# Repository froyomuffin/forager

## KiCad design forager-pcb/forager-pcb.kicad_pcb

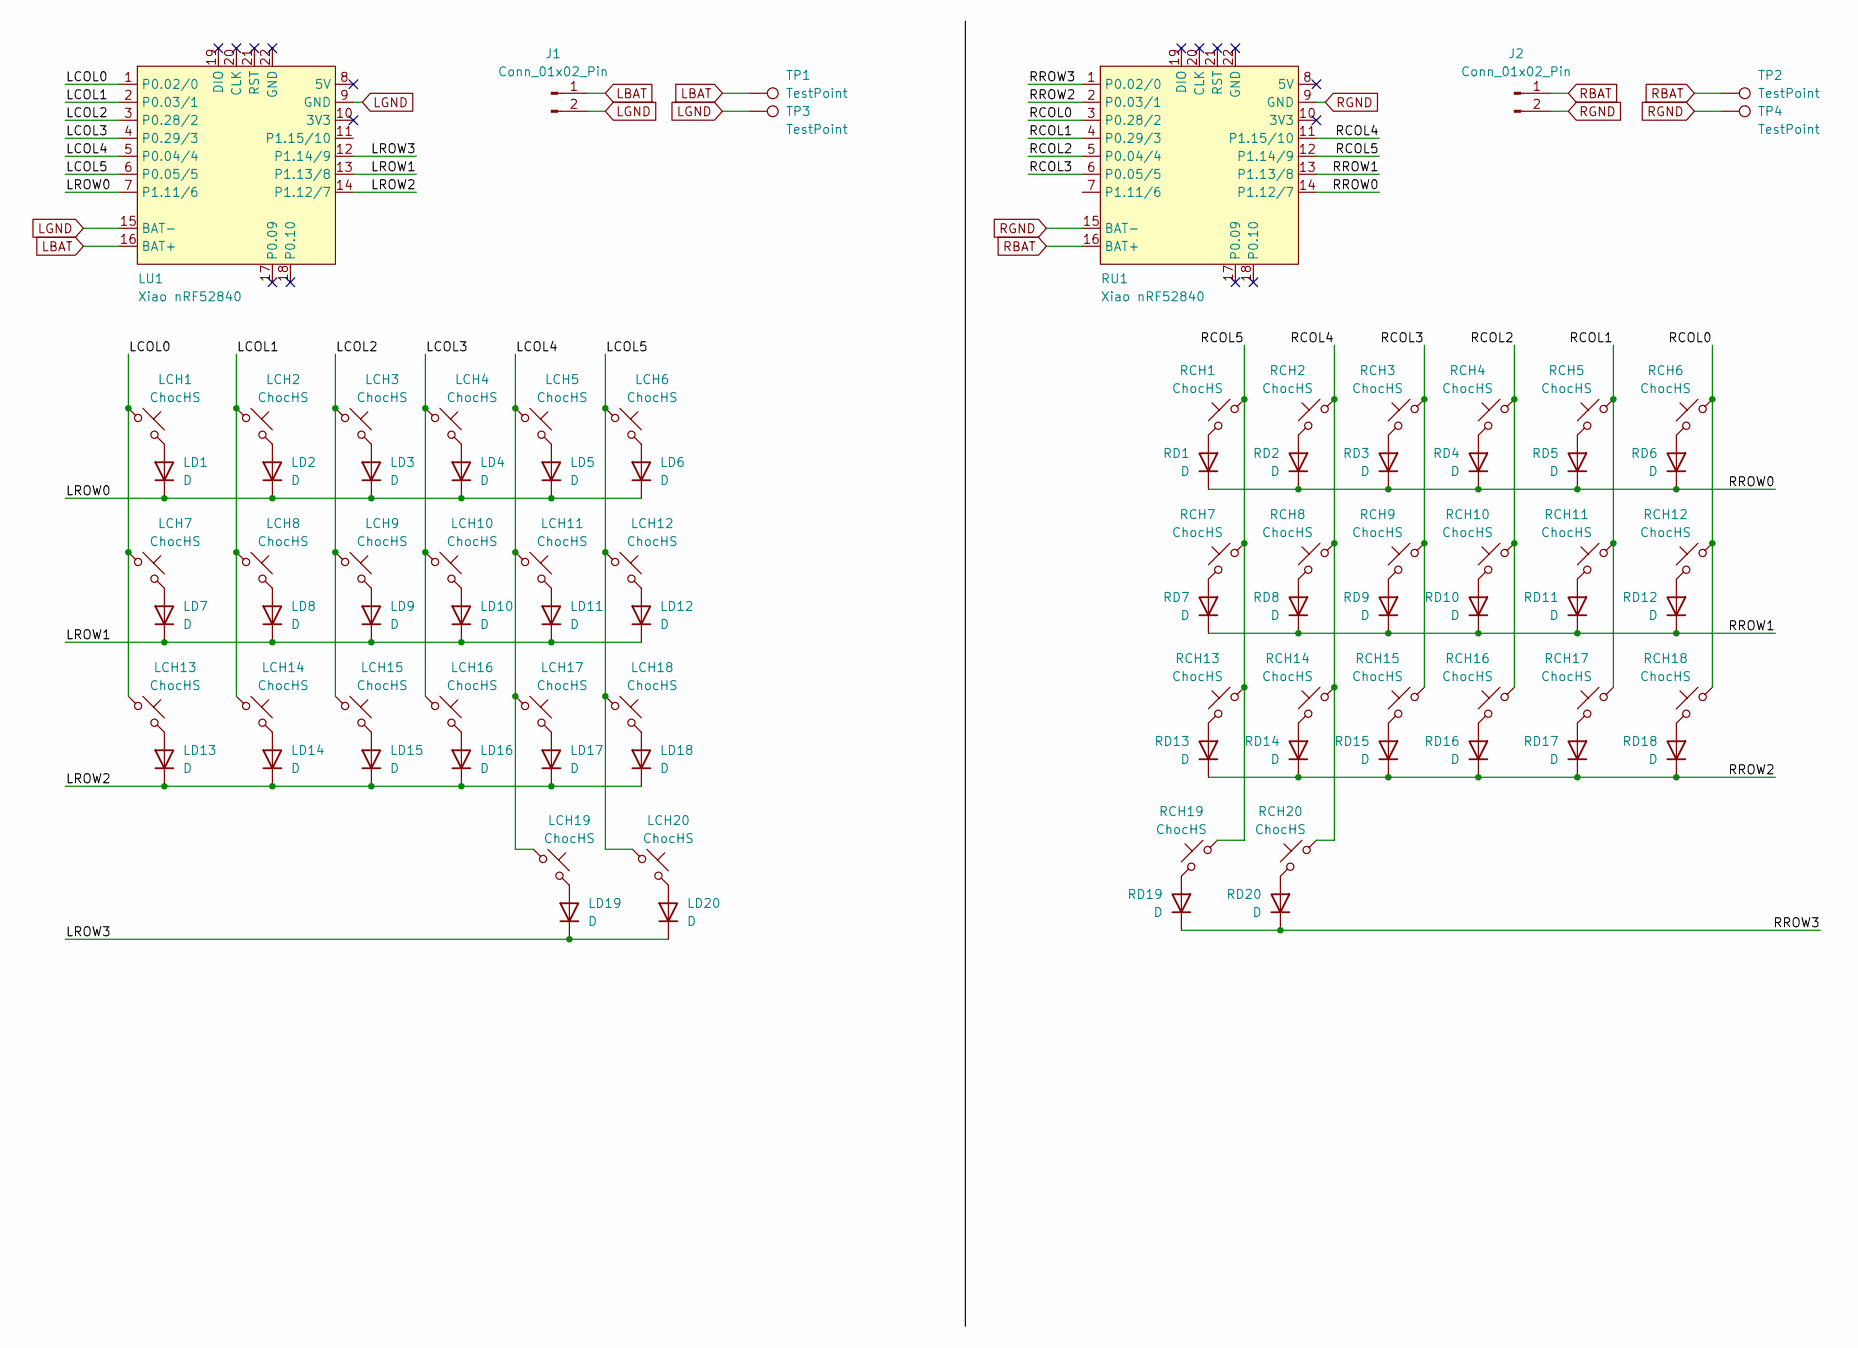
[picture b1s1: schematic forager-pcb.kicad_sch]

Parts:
J1, J2: Conn_01x02_Pin; JST_ACH_BM02B-ACHSS-GAN-ETF_1x02-1MP_P1.20mm_Vertical
LCH1, LCH2, LCH3, LCH4, LCH5, LCH6, LCH7, LCH8, LCH9, LCH10, LCH11, LCH12, LCH13, LCH14, LCH15, LCH16, LCH17, LCH18, LCH19, LCH20: ChocHS; Choc_v2_PG1353_socket
LD1, LD2, LD3, LD4, LD5, LD6, LD7, LD8, LD9, LD10, LD11, LD12, LD13, LD14, LD15, LD16, LD17, LD18, LD19, LD20: D; D_SOD-123
LU1: Xiao nRF52840; xiao-ble-smd-cutout
RCH1, RCH2, RCH3, RCH4, RCH5, RCH6, RCH7, RCH8, RCH9, RCH10, RCH11, RCH12, RCH13, RCH14, RCH15, RCH16, RCH17, RCH18, RCH19, RCH20: ChocHS; Choc_v2_PG1353_socket
RD1, RD2, RD3, RD4, RD5, RD6, RD7, RD8, RD9, RD10, RD11, RD12, RD13, RD14, RD15, RD16, RD17, RD18, RD19, RD20: D; D_SOD-123
RU1: Xiao nRF52840; xiao-ble-smd-cutout
TP1, TP2, TP3, TP4: TestPoint; TestPoint_Pad_D2.0mm

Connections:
/LCOL0: LCH1.1, LCH7.1, LCH13.1, LU1.1 (P0.02/0)
/LCOL1: LCH2.1, LCH8.1, LCH14.1, LU1.2 (P0.03/1)
/LCOL2: LCH3.1, LCH9.1, LCH15.1, LU1.3 (P0.28/2)
/LCOL3: LCH4.1, LCH10.1, LCH16.1, LU1.4 (P0.29/3)
/LCOL4: LCH5.1, LCH11.1, LCH17.1, LCH19.1, LU1.5 (P0.04/4)
/LCOL5: LCH6.1, LCH12.1, LCH18.1, LCH20.1, LU1.6 (P0.05/5)
/LROW0: LD1.1 (K), LD2.1 (K), LD3.1 (K), LD4.1 (K), LD5.1 (K), LD6.1 (K), LU1.7 (P1.11/6)
/LROW1: LD7.1 (K), LD8.1 (K), LD9.1 (K), LD10.1 (K), LD11.1 (K), LD12.1 (K), LU1.13 (P1.13/8)
/LROW2: LD13.1 (K), LD14.1 (K), LD15.1 (K), LD16.1 (K), LD17.1 (K), LD18.1 (K), LU1.14 (P1.12/7)
/LROW3: LD19.1 (K), LD20.1 (K), LU1.12 (P1.14/9)
/RCOL0: RCH6.1, RCH12.1, RCH18.1, RU1.3 (P0.28/2)
/RCOL1: RCH5.1, RCH11.1, RCH17.1, RU1.4 (P0.29/3)
/RCOL2: RCH4.1, RCH10.1, RCH16.1, RU1.5 (P0.04/4)
/RCOL3: RCH3.1, RCH9.1, RCH15.1, RU1.6 (P0.05/5)
/RCOL4: RCH2.1, RCH8.1, RCH14.1, RCH20.1, RU1.11 (P1.15/10)
/RCOL5: RCH1.1, RCH7.1, RCH13.1, RCH19.1, RU1.12 (P1.14/9)
/RROW0: RD1.1 (K), RD2.1 (K), RD3.1 (K), RD4.1 (K), RD5.1 (K), RD6.1 (K), RU1.14 (P1.12/7)
/RROW1: RD7.1 (K), RD8.1 (K), RD9.1 (K), RD10.1 (K), RD11.1 (K), RD12.1 (K), RU1.13 (P1.13/8)
/RROW2: RD13.1 (K), RD14.1 (K), RD15.1 (K), RD16.1 (K), RD17.1 (K), RD18.1 (K), RU1.2 (P0.03/1)
/RROW3: RD19.1 (K), RD20.1 (K), RU1.1 (P0.02/0)
LBAT: J1.1, LU1.16 (BAT+), TP1.1
LGND: J1.2, LU1.9 (GND), LU1.15 (BAT-), TP3.1
unnamed: LCH1.2, LD1.2 (A)
unnamed: LCH2.2, LD2.2 (A)
unnamed: LCH3.2, LD3.2 (A)
unnamed: LCH4.2, LD4.2 (A)
unnamed: LCH5.2, LD5.2 (A)
unnamed: LCH6.2, LD6.2 (A)
unnamed: LCH7.2, LD7.2 (A)
unnamed: LCH8.2, LD8.2 (A)
unnamed: LCH9.2, LD9.2 (A)
unnamed: LCH10.2, LD10.2 (A)
unnamed: LCH11.2, LD11.2 (A)
unnamed: LCH12.2, LD12.2 (A)
unnamed: LCH13.2, LD13.2 (A)
unnamed: LCH14.2, LD14.2 (A)
unnamed: LCH15.2, LD15.2 (A)
unnamed: LCH16.2, LD16.2 (A)
unnamed: LCH17.2, LD17.2 (A)
unnamed: LCH18.2, LD18.2 (A)
unnamed: LCH19.2, LD19.2 (A)
unnamed: LCH20.2, LD20.2 (A)
unnamed: RCH1.2, RD1.2 (A)
unnamed: RCH2.2, RD2.2 (A)
unnamed: RCH3.2, RD3.2 (A)
unnamed: RCH4.2, RD4.2 (A)
unnamed: RCH5.2, RD5.2 (A)
unnamed: RCH6.2, RD6.2 (A)
unnamed: RCH7.2, RD7.2 (A)
unnamed: RCH8.2, RD8.2 (A)
unnamed: RCH9.2, RD9.2 (A)
unnamed: RCH10.2, RD10.2 (A)
unnamed: RCH11.2, RD11.2 (A)
unnamed: RCH12.2, RD12.2 (A)
unnamed: RCH13.2, RD13.2 (A)
unnamed: RCH14.2, RD14.2 (A)
unnamed: RCH15.2, RD15.2 (A)
unnamed: RCH16.2, RD16.2 (A)
unnamed: RCH17.2, RD17.2 (A)
unnamed: RCH18.2, RD18.2 (A)
unnamed: RCH19.2, RD19.2 (A)
unnamed: RCH20.2, RD20.2 (A)
RBAT: J2.1, RU1.16 (BAT+), TP2.1
RGND: J2.2, RU1.9 (GND), RU1.15 (BAT-), TP4.1

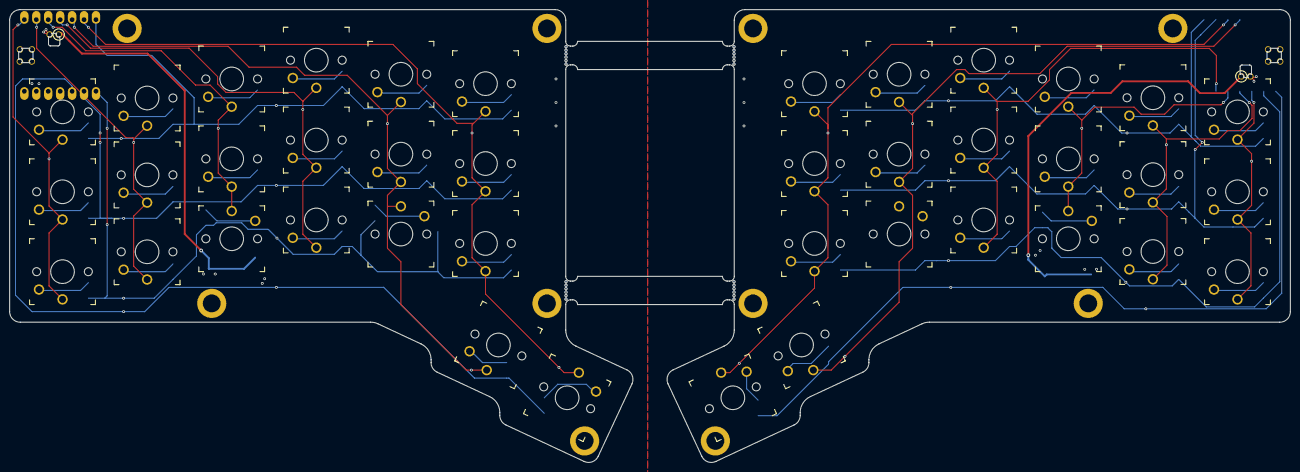
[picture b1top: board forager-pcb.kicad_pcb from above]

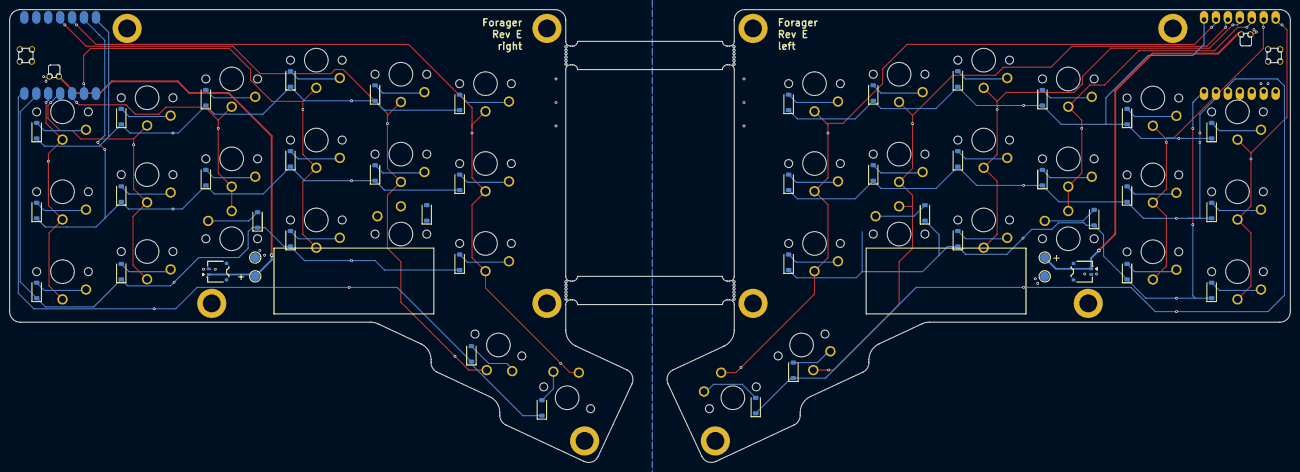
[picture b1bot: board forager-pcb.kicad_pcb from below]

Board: 2 copper layers, 272.5 x 96.3 mm, 88 parts (88 on the bottom side), 64 nets.

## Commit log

2024-12-15 Add extra column and remove all traces
2024-12-18 Giving up on meaningful commit breakdown
2024-12-22 Add extra row to schematic and update PCB
2024-12-22 Extend PCB
2024-12-22 Move out components to edges and clear all traces
2024-12-22 Move in new columns
2024-12-22 Set left diodes
2024-12-22 Fix bad annotation
2024-12-23 Set right diodes
2024-12-23 Swap to choc v2 comparible centerhole
2024-12-23 Swap to solder sockets
2025-04-26 Upgrade version
2025-04-26 Align switches
2025-04-28 Per switch diode
2025-04-28 Internal switch routes
2025-04-28 Cross switch diodes
2025-04-29 Top cross switches
2025-04-29 Top to controller
2025-04-29 Connect power
2025-04-29 Connect remaining to controller
2025-04-29 Add fuck up holes
2025-04-30 Move some diodes for battery
2025-05-10 Move some pins out of battery section
2025-05-10 Better battery connection
2025-05-10 Add through holes for controller alignment
2025-05-10 Cleanup all the things
2025-05-11 Handle right side + new battery cutouts
